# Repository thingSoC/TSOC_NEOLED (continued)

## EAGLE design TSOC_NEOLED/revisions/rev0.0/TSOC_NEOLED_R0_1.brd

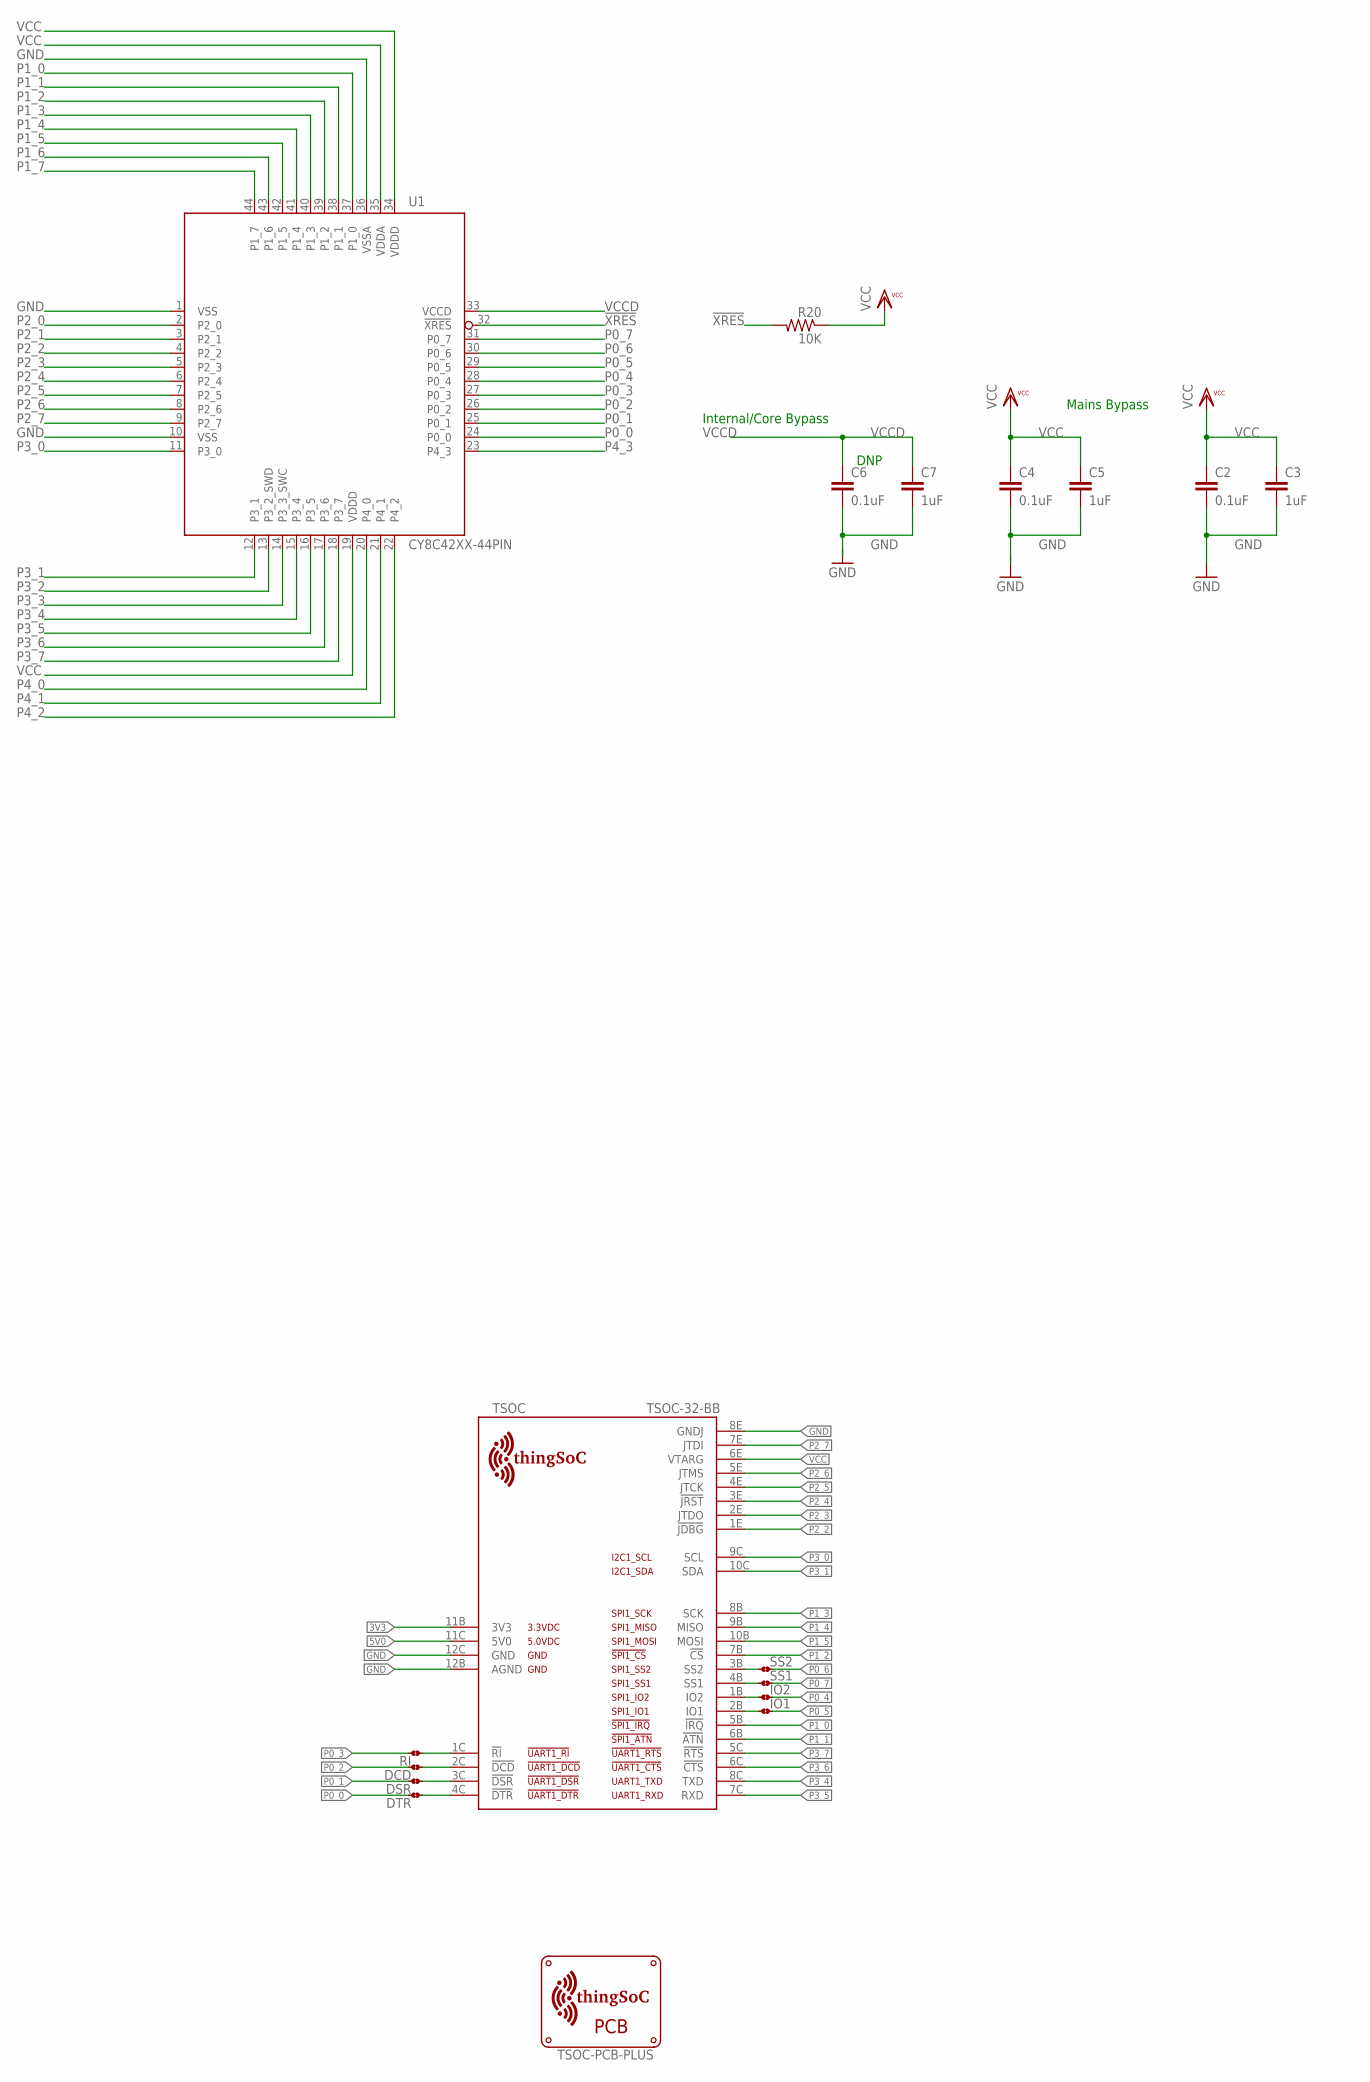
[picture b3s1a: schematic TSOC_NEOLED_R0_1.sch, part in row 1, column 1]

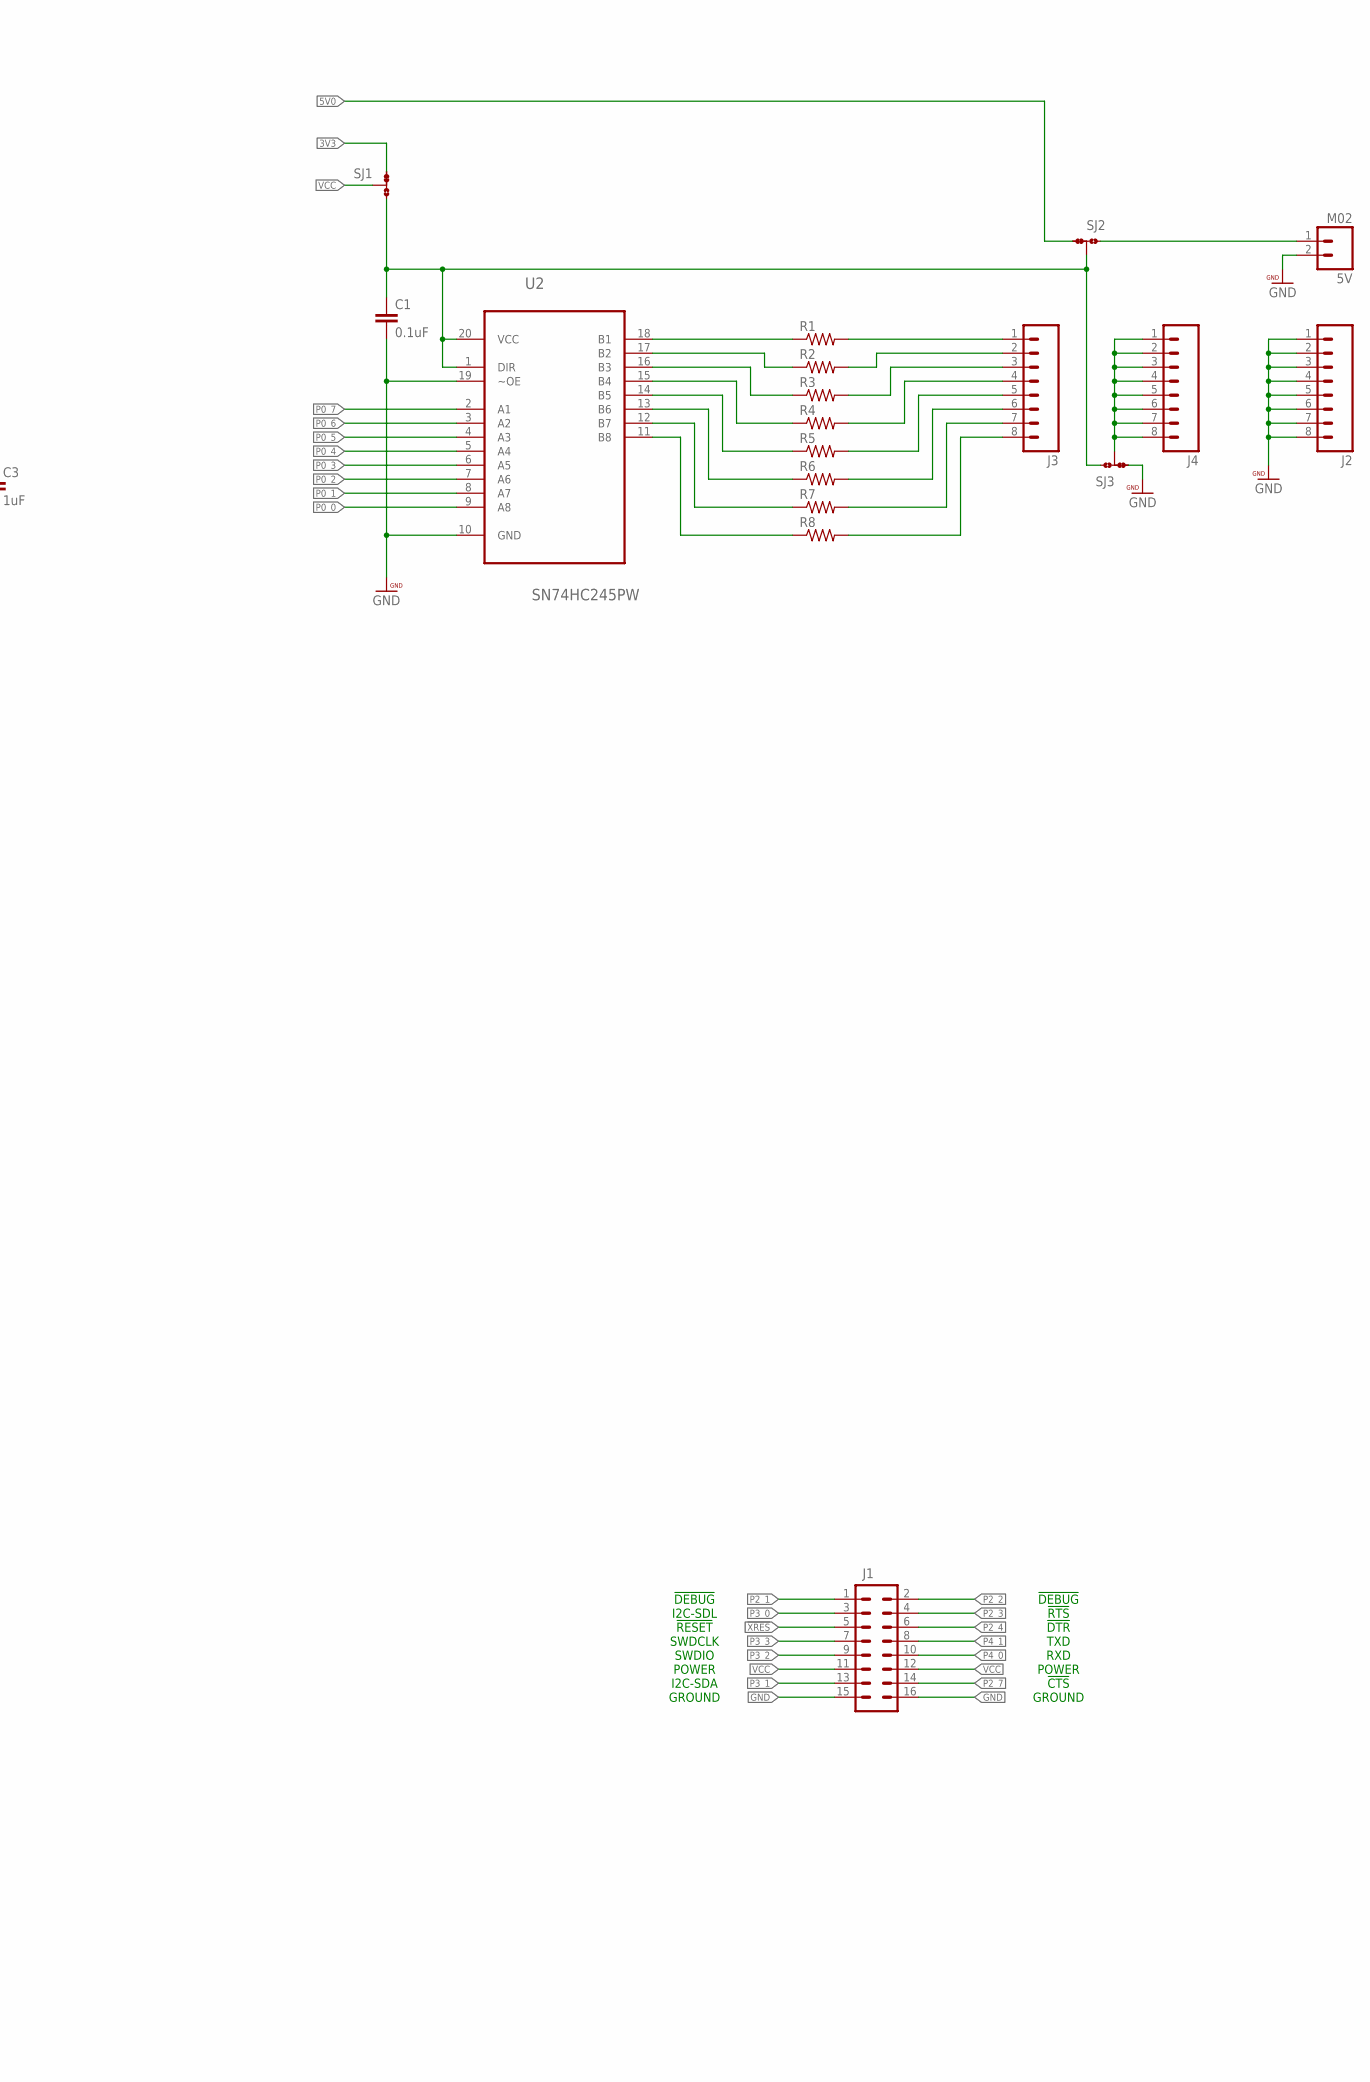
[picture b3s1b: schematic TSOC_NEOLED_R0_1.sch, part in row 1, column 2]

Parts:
5V: M02; 1X02
C1, C2, C4, C6: 0.1uF; 0603-CAP
C3, C5, C7: 1uF; 0603-CAP
DCD: JMP-2-NO
DSR: JMP-2-NO
DTR: JMP-2-NO
IO1, IO2: JMP-2-NO
J1: M08X2; 2X8
J2, J3, J4: M08; 1X08_ROUND
R1, R2, R3, R4, R5, R6, R7, R8: RESISTOR0603-RES; 0603-RES
R20: 10K; 0603-RES
RI: JMP-2-NO
SJ1, SJ2, SJ3: JMP-3-1_2
SS1, SS2: JMP-2-NO
TSOC: TSOC-32-BB; TSOC-BB-S32
U1: CY8C42XX-44PIN; TQFP-10X10-44
U2: SN74HC245PW; SOP65P640X120-20N
U$3: TSOC-PCB-PLUS; TSOC-BB-BRD-PLUS

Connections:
3V3: SJ1.1, TSOC.11B (3V3)
5V0: SJ2.1, TSOC.11C (5V0)
!DCD: DCD.1, TSOC.2C (!DCD)
!DSR: DSR.1, TSOC.3C (!DSR)
!DTR: DTR.1, TSOC.4C (!DTR)
!R!: RI.1, TSOC.1C (!RI)
!XRES: J1.5, R20.2, U1.32 (!XRES)
GND: 5V.2, C1.2, C2.2, C3.2, C4.2, C5.2, C6.2, C7.2, J1.15, J1.16, J2.1, J2.2, J2.3, J2.4, J2.5, J2.6, J2.7, J2.8, SJ3.1, TSOC.8E (GNDJ), TSOC.12B (AGND), TSOC.12C (GND), U1.1 (VSS), U1.10 (VSS), U1.36 (VSSA), U2.10 (GND), U2.19 (~OE)
IO1: IO1.1, TSOC.2B (IO1)
IO2: IO2.1, TSOC.1B (IO2)
unnamed: J3.1, R1.2
unnamed: J3.2, R2.2
unnamed: J3.3, R3.2
unnamed: J3.4, R4.2
unnamed: J3.5, R5.2
unnamed: J3.6, R6.2
unnamed: J3.7, R7.2
unnamed: J3.8, R8.2
unnamed: R1.1, U2.18 (B1)
unnamed: R2.1, U2.17 (B2)
unnamed: R3.1, U2.16 (B3)
unnamed: R4.1, U2.15 (B4)
unnamed: R5.1, U2.14 (B5)
unnamed: R6.1, U2.13 (B6)
unnamed: R7.1, U2.12 (B7)
unnamed: R8.1, U2.11 (B8)
P0_0: DTR.2, U1.24 (P0_0), U2.9 (A8)
P0_1: DSR.2, U1.25 (P0_1), U2.8 (A7)
P0_2: DCD.2, U1.26 (P0_2), U2.7 (A6)
P0_3: RI.2, U1.27 (P0_3), U2.6 (A5)
P0_4: IO2.2, U1.28 (P0_4), U2.5 (A4)
P0_5: IO1.2, U1.29 (P0_5), U2.4 (A3)
P0_6: SS2.2, U1.30 (P0_6), U2.3 (A2)
P0_7: SS1.2, U1.31 (P0_7), U2.2 (A1)
P1_0: TSOC.5B (!IRQ), U1.37 (P1_0)
P1_1: TSOC.6B (!ATN), U1.38 (P1_1)
P1_2: TSOC.7B (!CS), U1.39 (P1_2)
P1_3: TSOC.8B (SCK), U1.40 (P1_3)
P1_4: TSOC.9B (MISO), U1.41 (P1_4)
P1_5: TSOC.10B (MOSI), U1.42 (P1_5)
P1_6: U1.43 (P1_6)
P1_7: U1.44 (P1_7)
P2_0: U1.2 (P2_0)
P2_1: J1.1, U1.3 (P2_1)
P2_2: J1.2, TSOC.1E (!JDBG), U1.4 (P2_2)
P2_3: J1.4, TSOC.2E (JTDO), U1.5 (P2_3)
P2_4: J1.6, TSOC.3E (!JRST), U1.6 (P2_4)
P2_5: TSOC.4E (JTCK), U1.7 (P2_5)
P2_6: TSOC.5E (JTMS), U1.8 (P2_6)
P2_7: J1.14, TSOC.7E (JTDI), U1.9 (P2_7)
P3_0: J1.3, TSOC.9C (SCL), U1.11 (P3_0)
P3_1: J1.13, TSOC.10C (SDA), U1.12 (P3_1)
P3_2: J1.9, U1.13 (P3_2_SWD)
P3_3: J1.7, U1.14 (P3_3_SWC)
P3_4: TSOC.8C (TXD), U1.15 (P3_4)
P3_5: TSOC.7C (RXD), U1.16 (P3_5)
P3_6: TSOC.6C (!CTS), U1.17 (P3_6)
P3_7: TSOC.5C (!RTS), U1.18 (P3_7)
P4_0: J1.10, U1.20 (P4_0)
P4_1: J1.8, U1.21 (P4_1)
P4_2: U1.22 (P4_2)
P4_3: U1.23 (P4_3)
SS1: SS1.1, TSOC.4B (SS1)
SS2: SS2.1, TSOC.3B (SS2)
VCC: C2.1, C3.1, C4.1, C5.1, J1.11, J1.12, R20.1, SJ1.2, TSOC.6E (VTARG), U1.19 (VDDD), U1.34 (VDDD), U1.35 (VDDA)
VCCD: C6.1, C7.1, U1.33 (VCCD)
VEXT: 5V.1, SJ2.3
VIN: C1.1, SJ1.3, SJ2.2, SJ3.3, U2.1 (DIR), U2.20 (VCC)
VOUT: J4.1, J4.2, J4.3, J4.4, J4.5, J4.6, J4.7, J4.8, SJ3.2

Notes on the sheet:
DNP
Internal/Core Bypass
Mains Bypass
I2C-SDA
I2C-SDL
!RESET
SWDCLK
SWDIO
POWER
GROUND
!DEBUG
!RTS
!CTS
!DTR
TXD
RXD

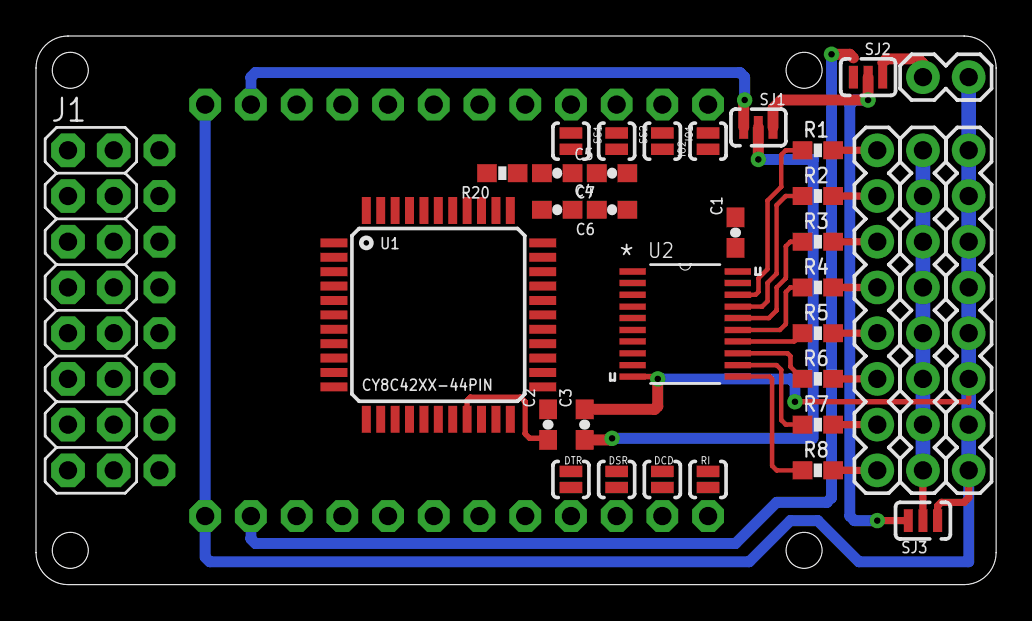
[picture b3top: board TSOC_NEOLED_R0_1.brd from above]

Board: 2 copper layers, 53.3 x 30.5 mm, 36 parts (0 on the bottom side), 64 nets.

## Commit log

2016-04-29 update images
2016-05-23 update BOM
2016-06-27 update firmware
2016-06-27 update gerbers
2016-07-21 update descriptions
2016-07-21 update tutorial
2016-07-26 update to V2_0
2016-08-08 add product images
2016-08-08 add servo example
2017-01-16 update documetation
2017-02-28 update docs
2020-06-16 rev 1.2 update
